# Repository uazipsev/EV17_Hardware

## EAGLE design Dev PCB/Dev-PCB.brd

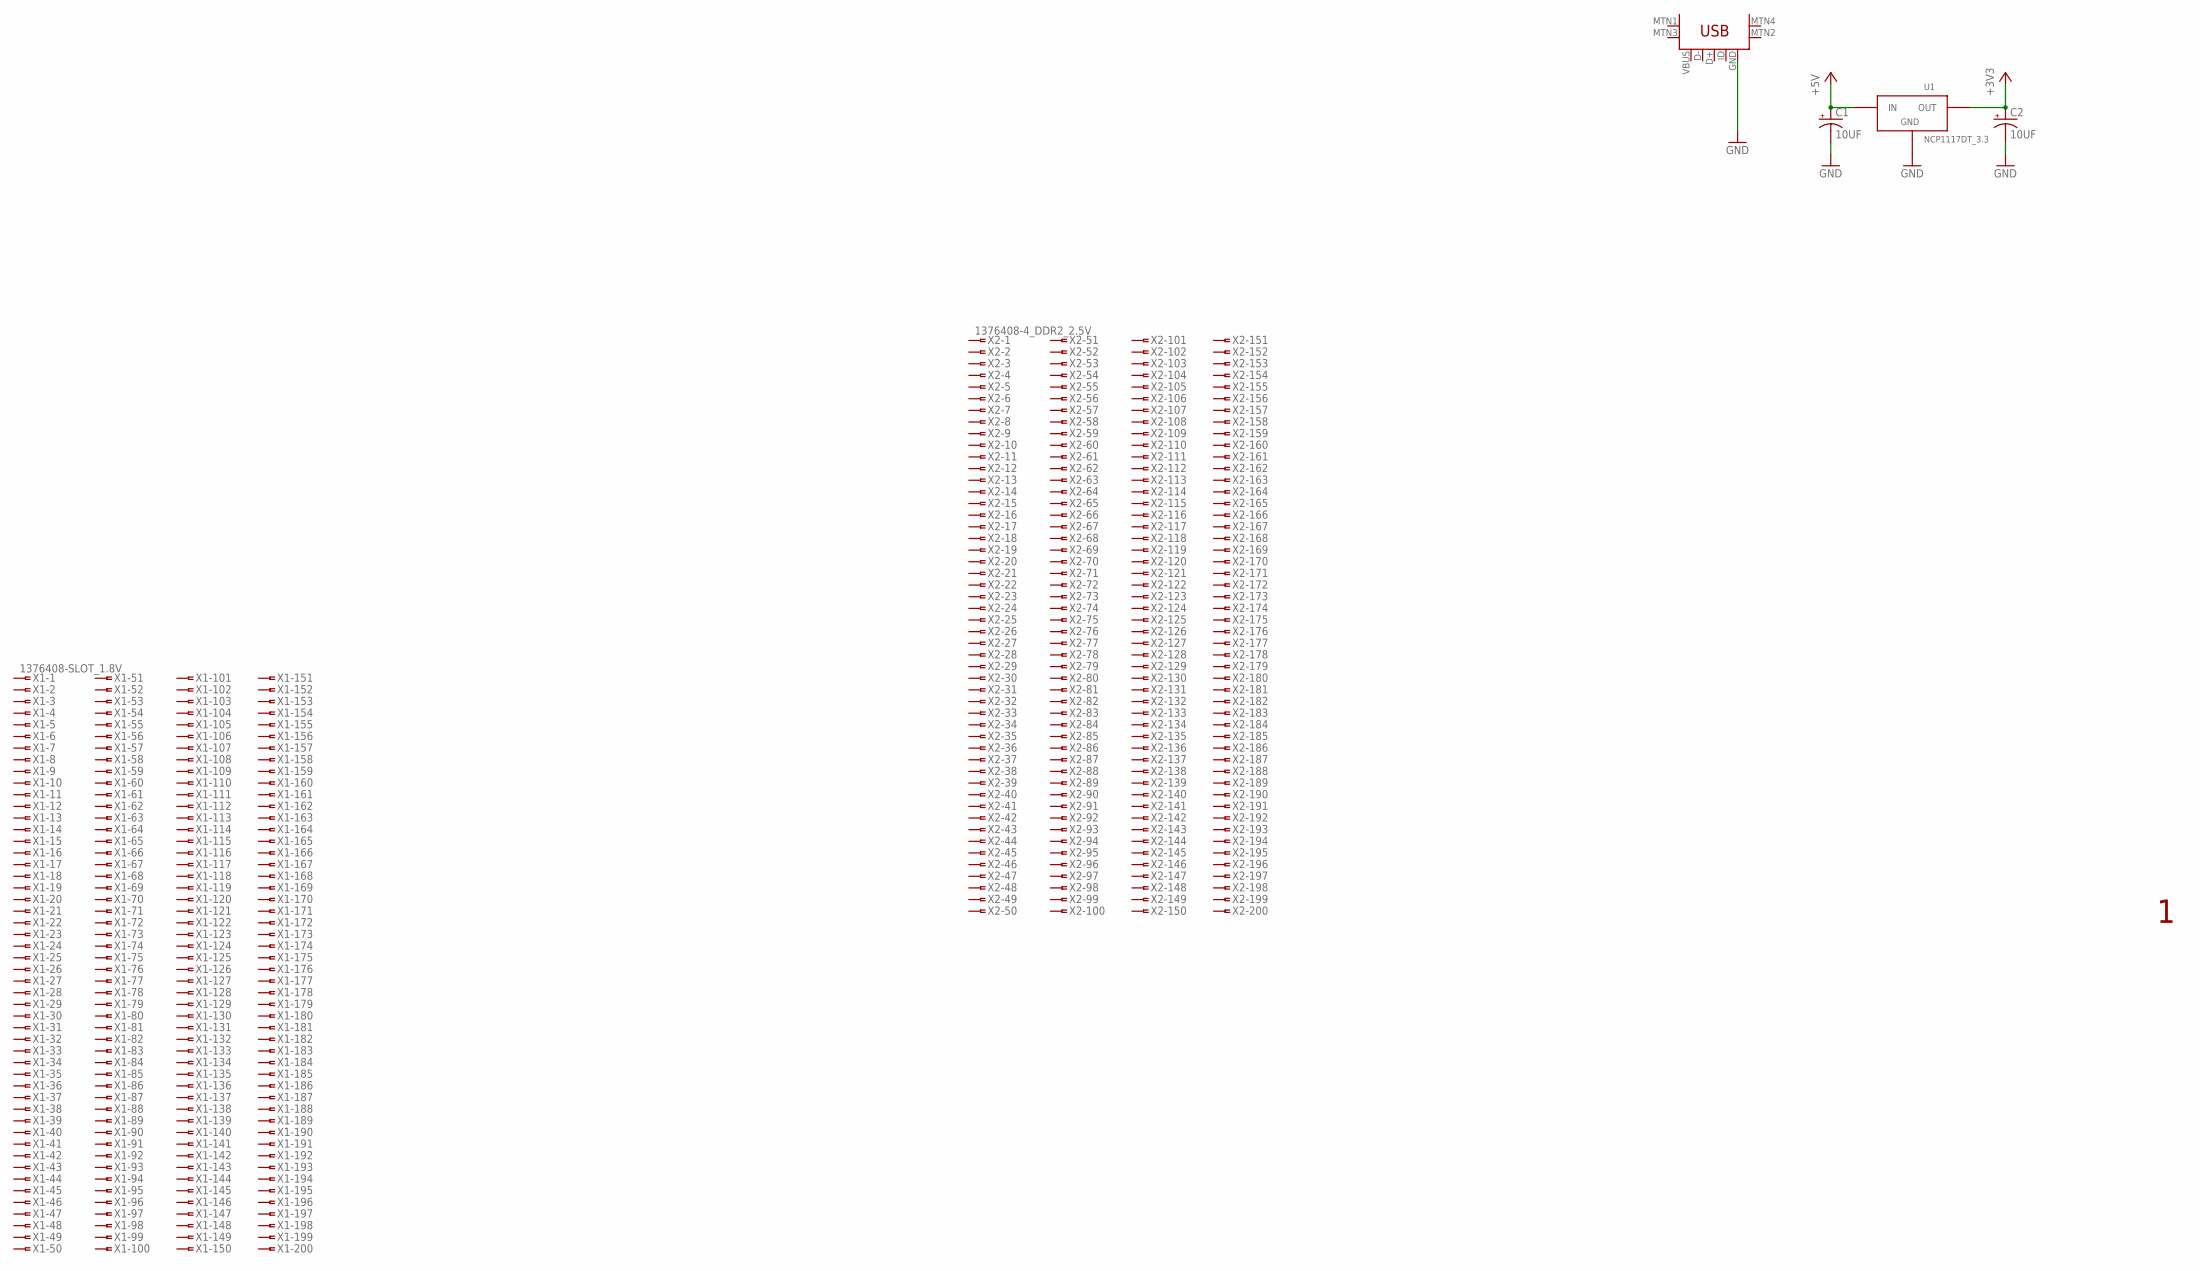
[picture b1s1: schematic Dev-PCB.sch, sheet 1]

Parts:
C1, C2: 10UF; EIA3216-16V
U1: NCP1117DT_3.3; DPAK
U$1: USB-MINIB-5PIN; USB-MINIB
X1: 1376408-SLOT_1.8V; SLOT-1376408-1_1.8V
X2: 1376408-4_DDR2_2.5V; 1-1376408-4

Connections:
+3V3: C2.A (+), U1.2 (OUT)
+5V: C1.A (+), U1.3 (IN)
GND: C1.C (+1), C2.C (+1), U1.1 (GND), U$1.GND

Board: 2 copper layers, 6 parts (0 on the bottom side), 3 nets, no tracks yet.

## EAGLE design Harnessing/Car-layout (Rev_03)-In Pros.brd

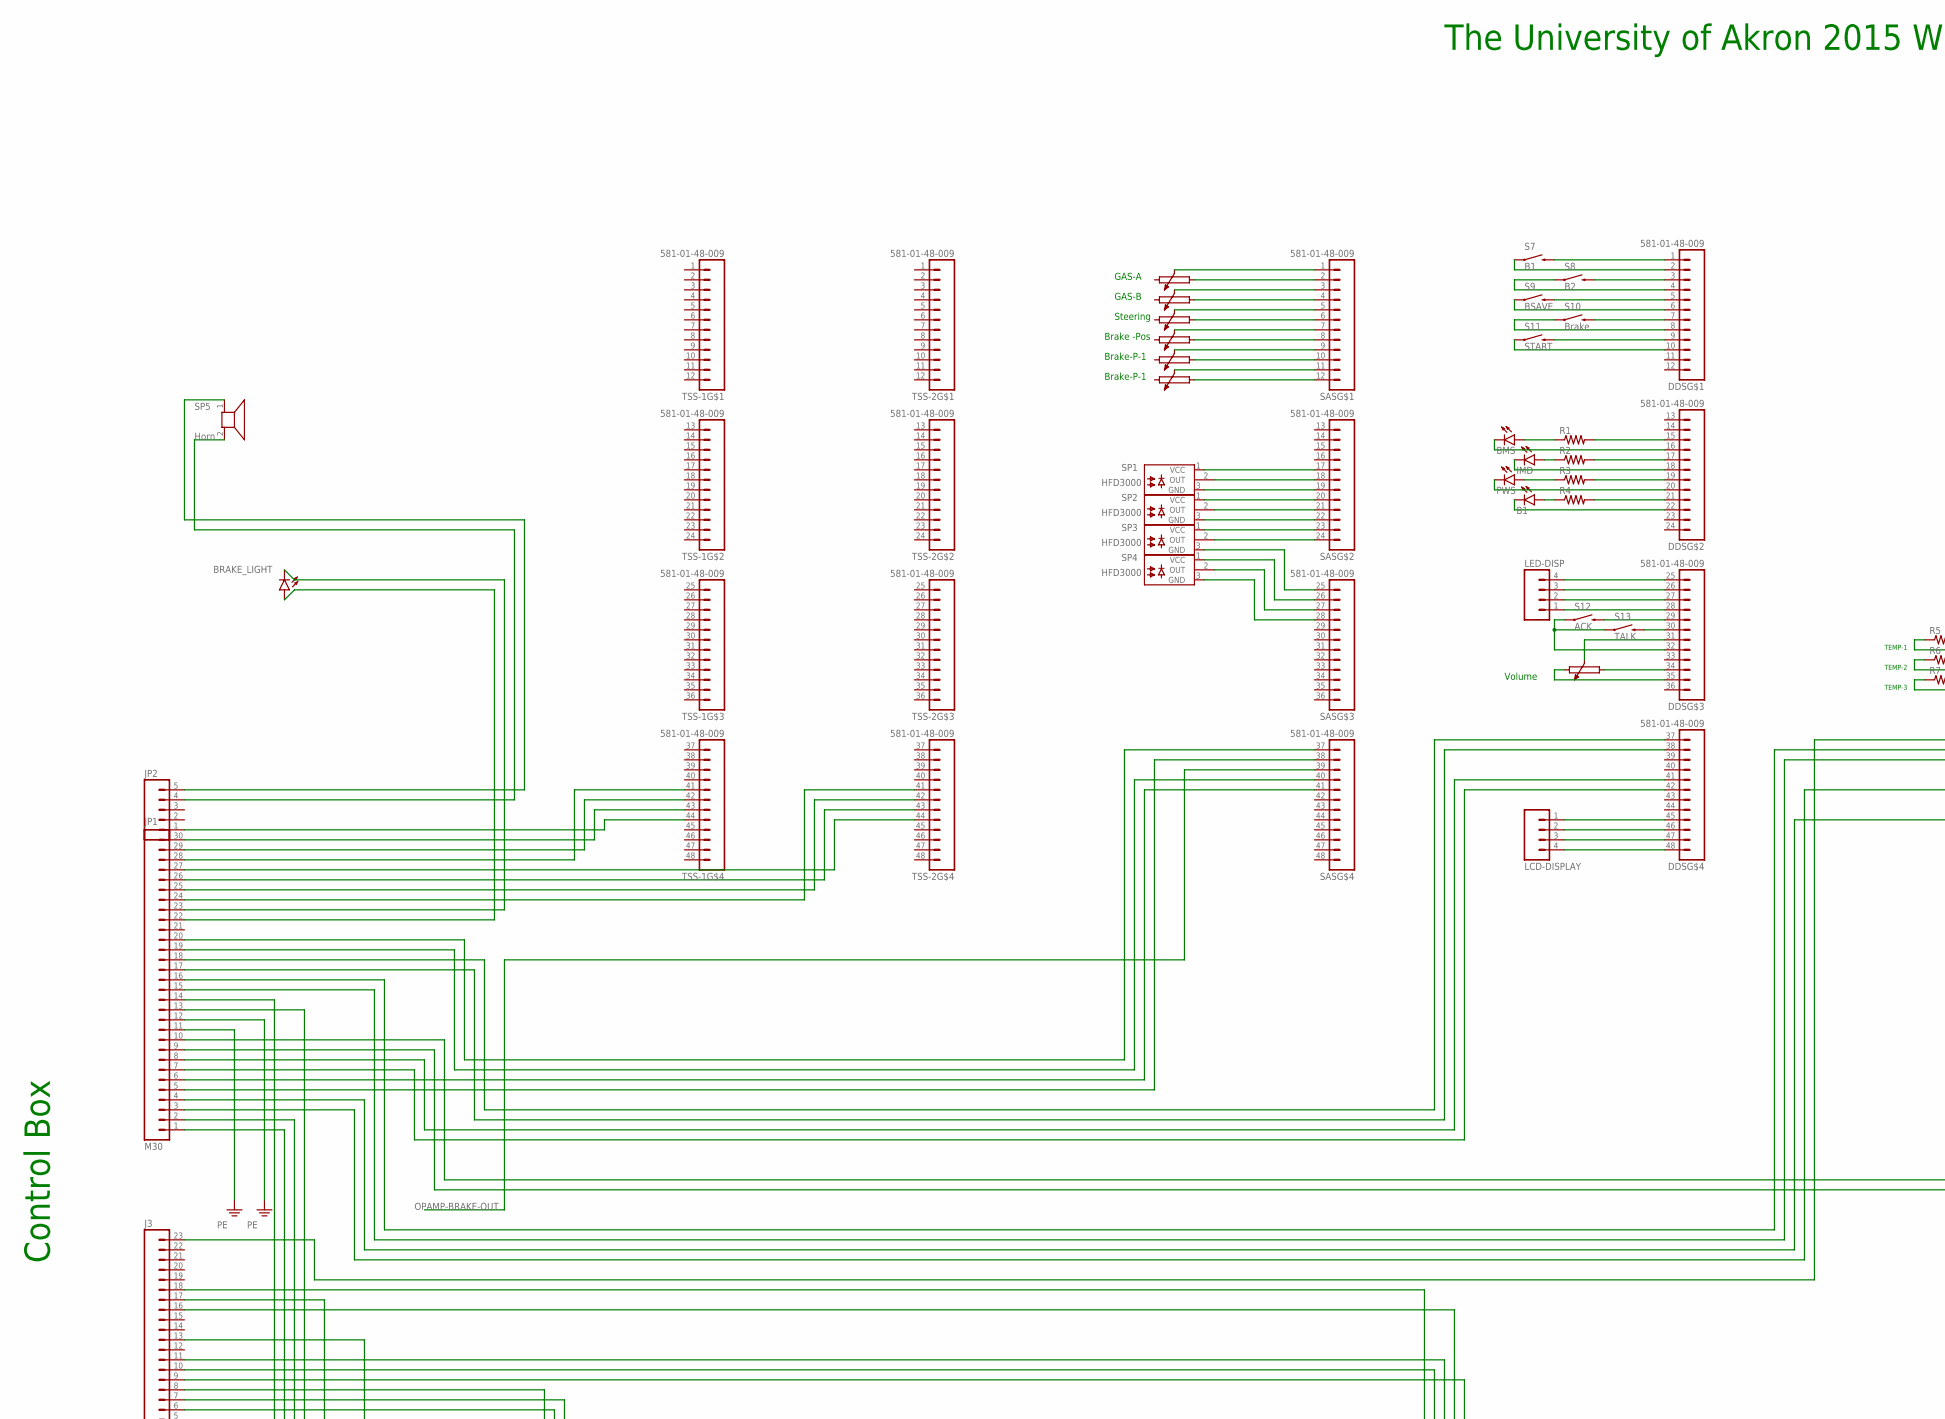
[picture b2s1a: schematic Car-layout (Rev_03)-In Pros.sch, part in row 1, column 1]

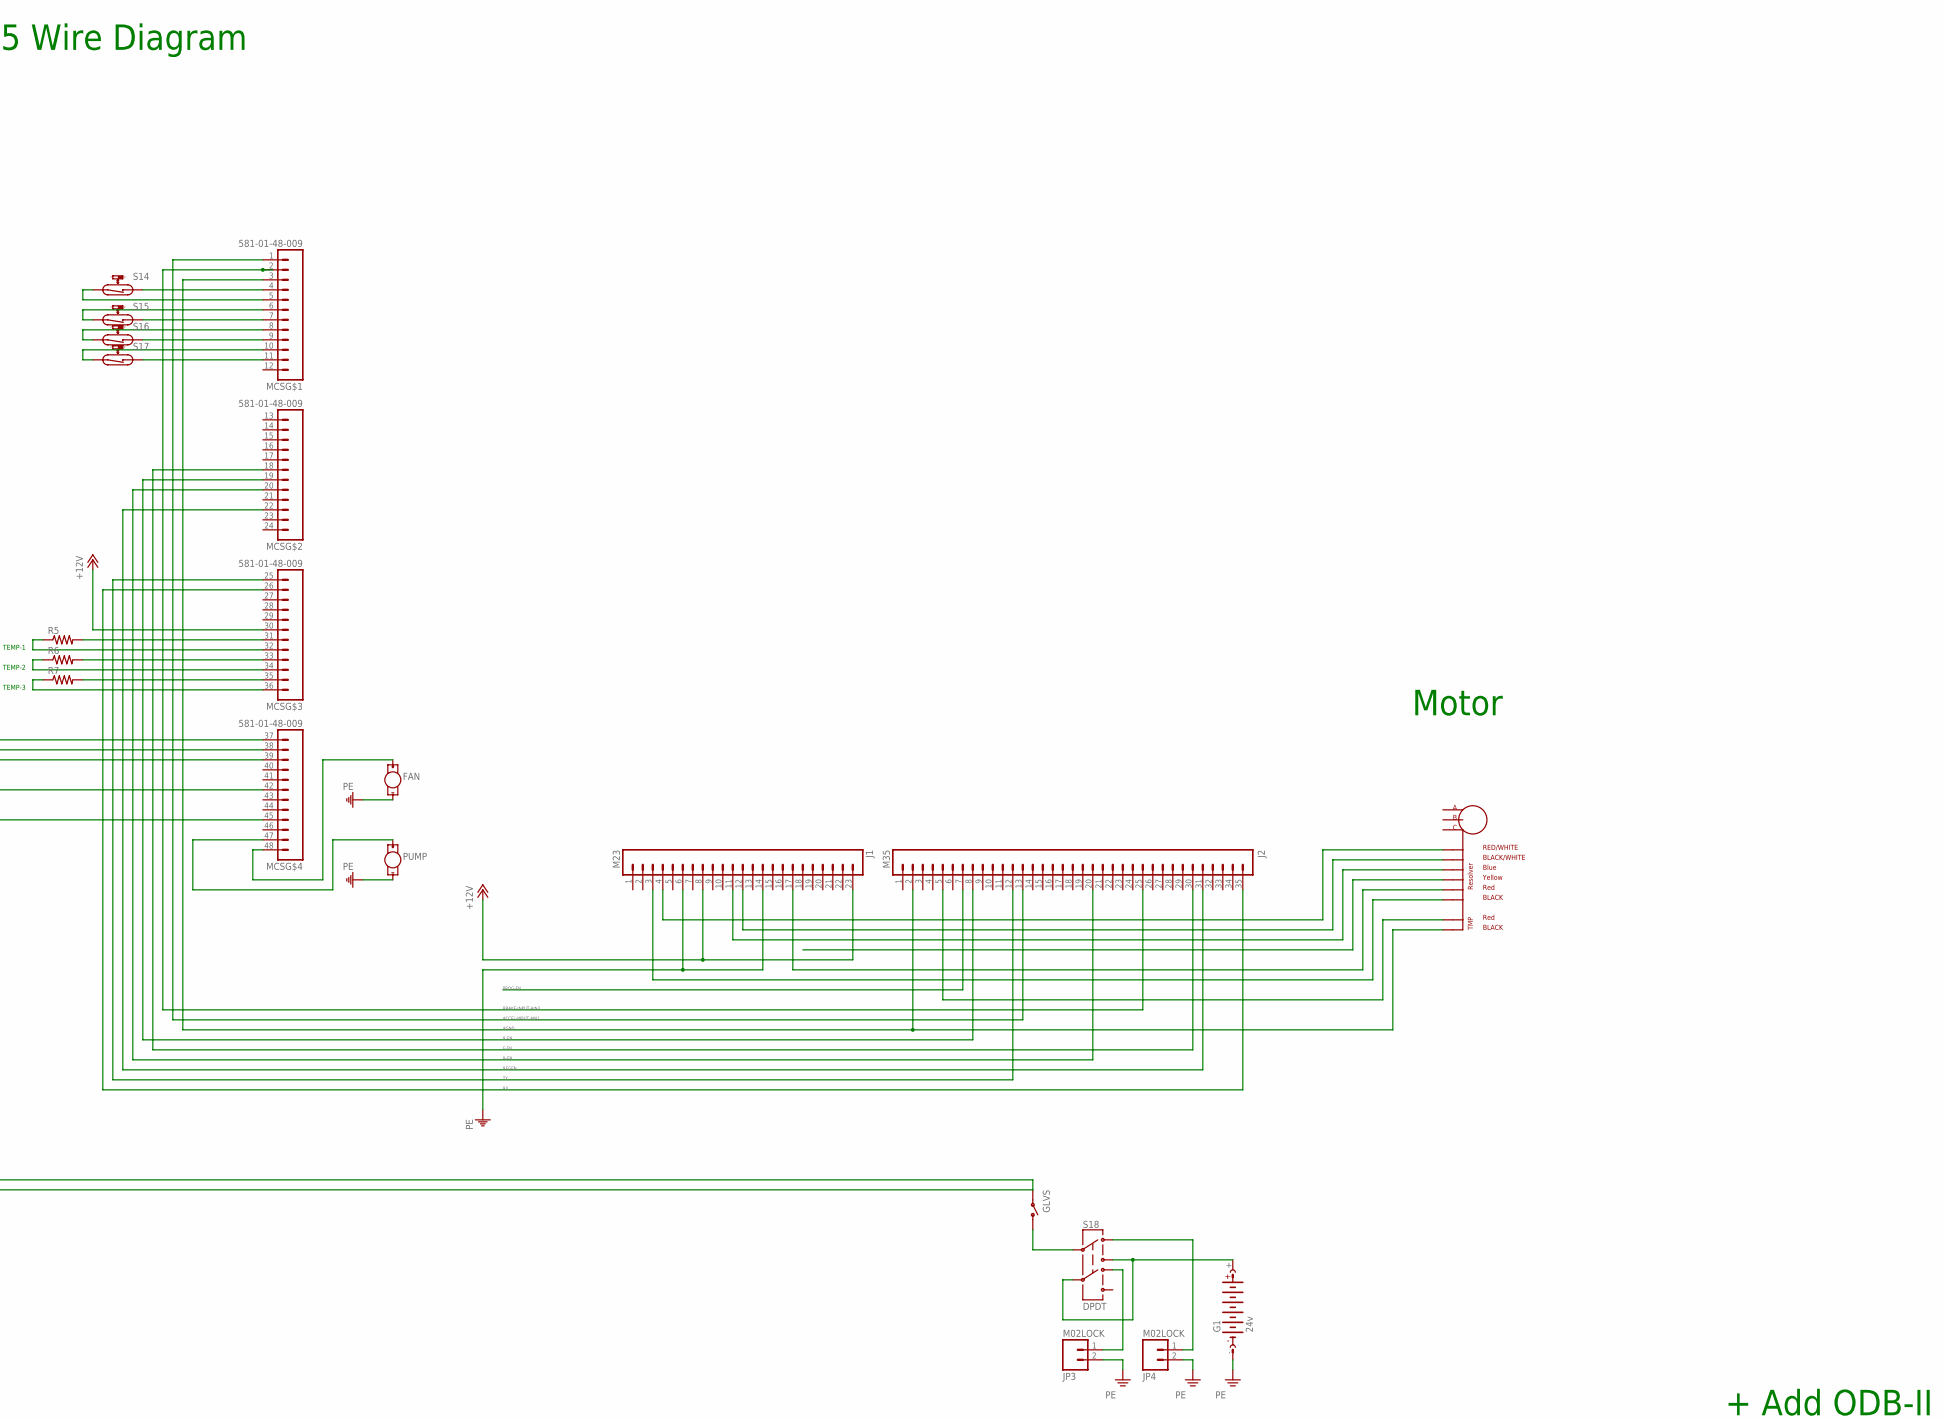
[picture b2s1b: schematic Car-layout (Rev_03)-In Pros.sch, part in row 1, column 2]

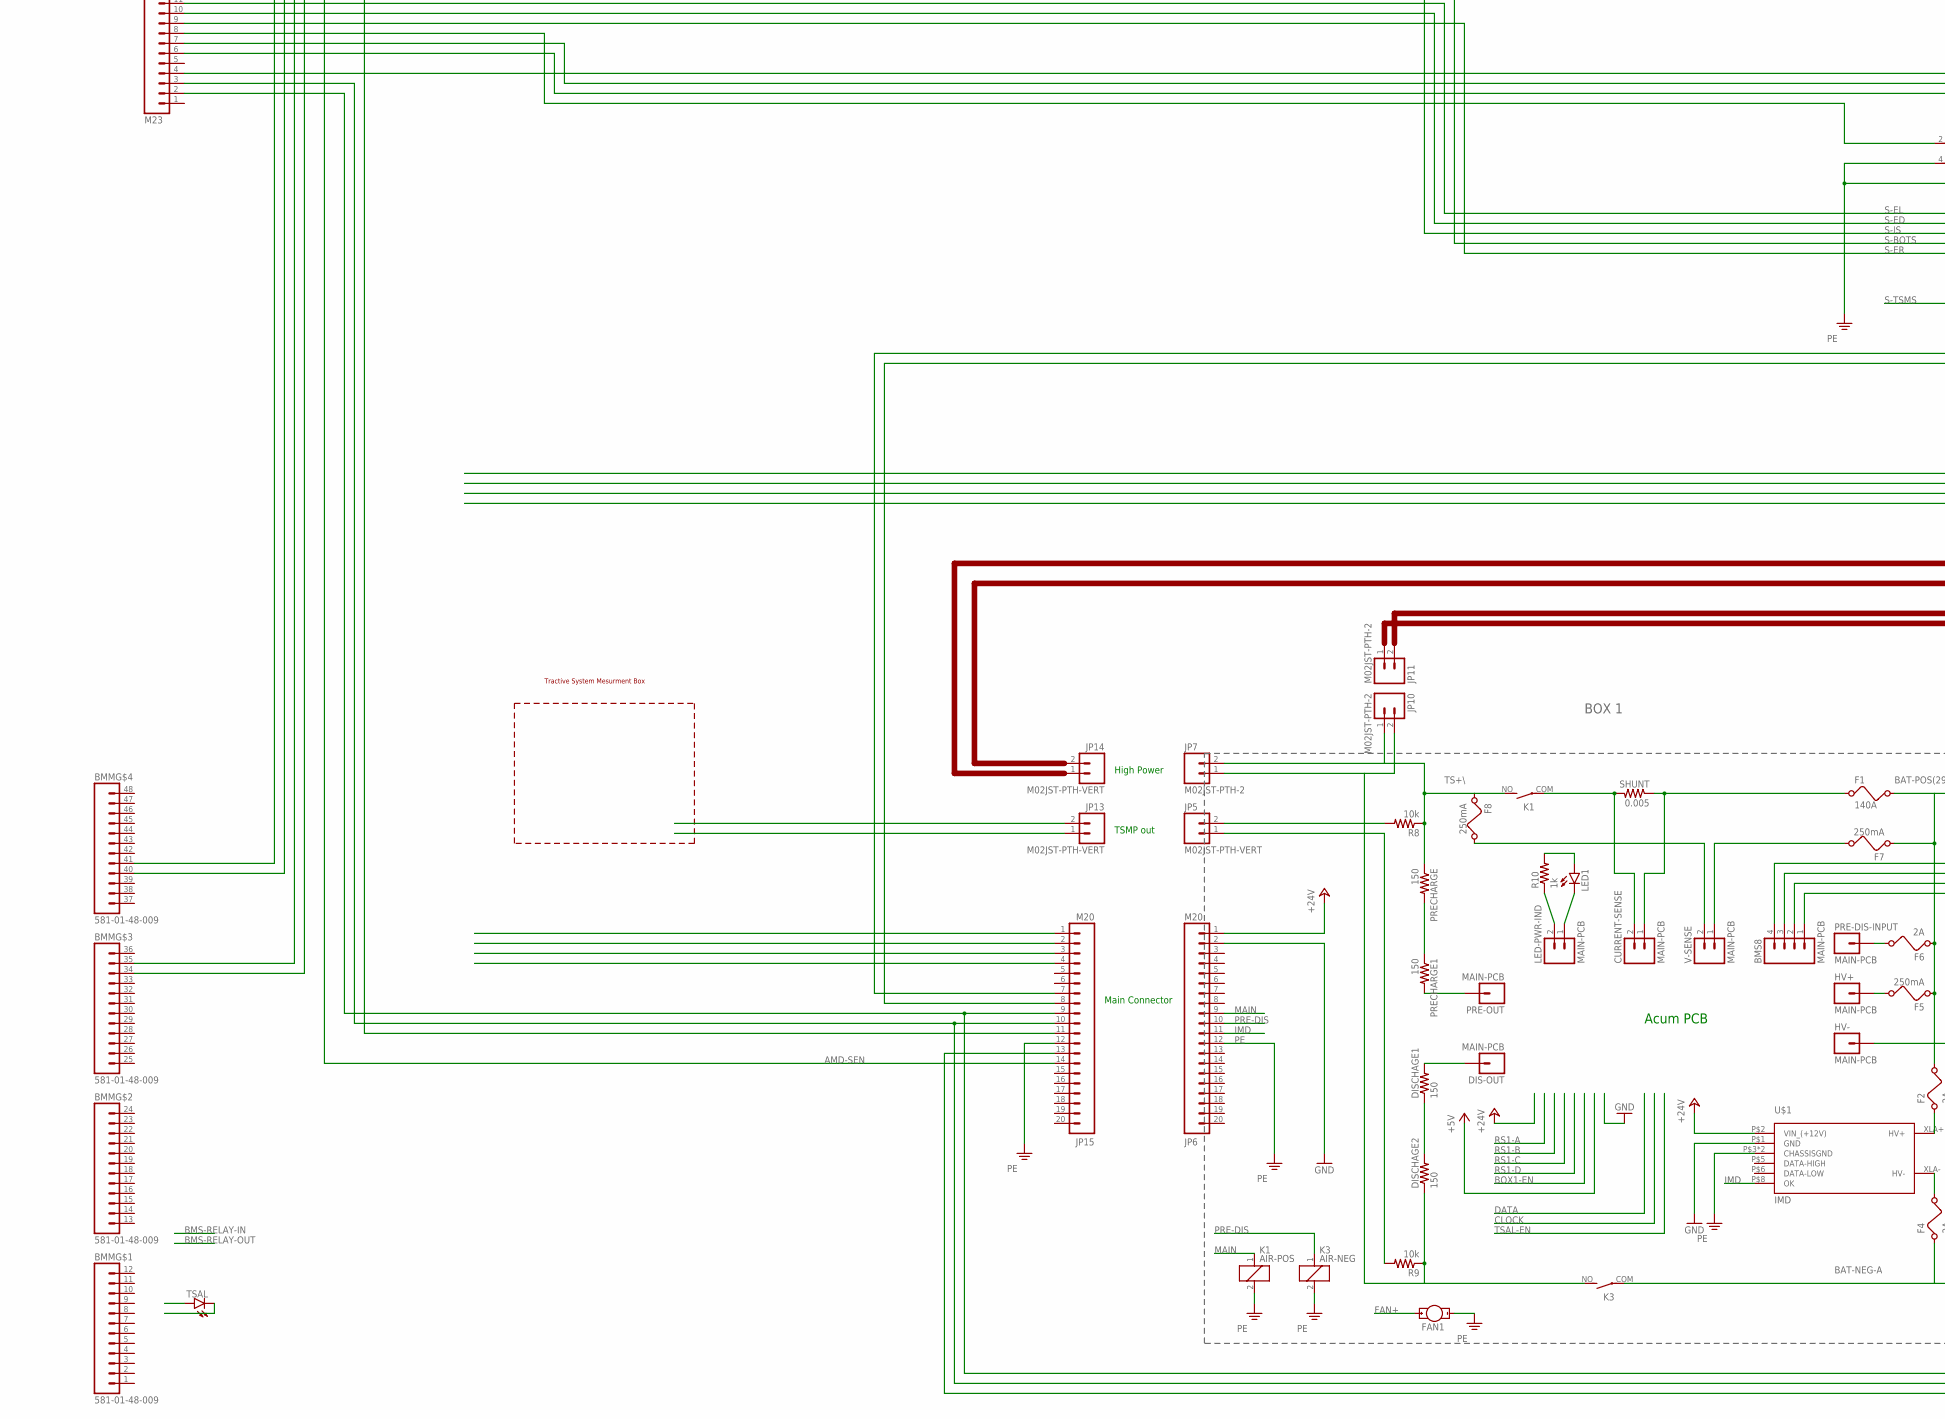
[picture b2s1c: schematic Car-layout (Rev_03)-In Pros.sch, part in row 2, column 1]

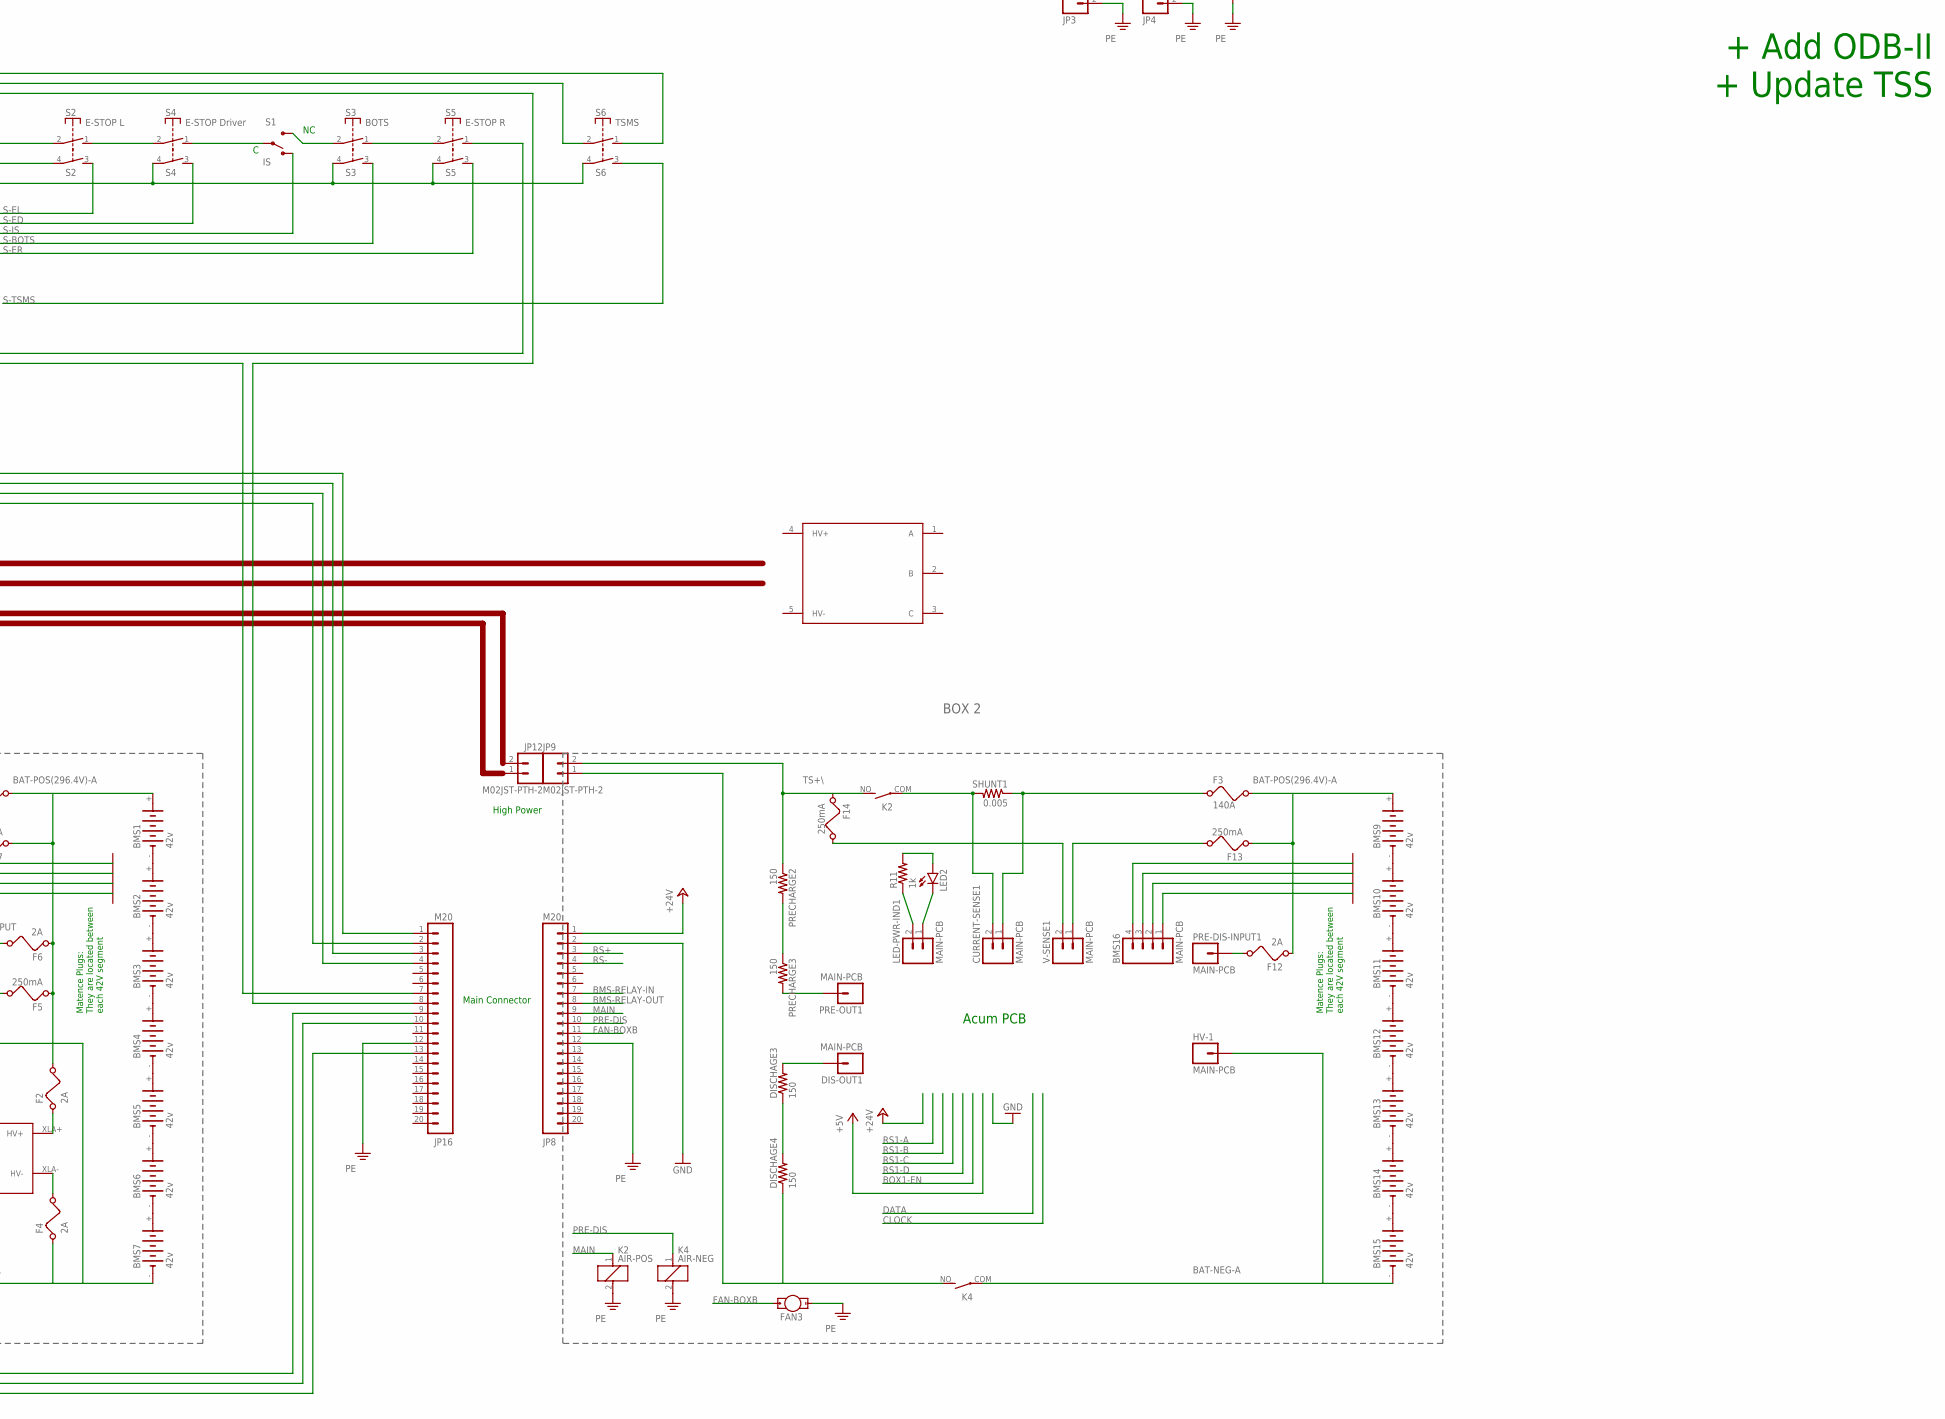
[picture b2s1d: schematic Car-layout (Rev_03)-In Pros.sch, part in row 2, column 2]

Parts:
B1: LED5MM
BMM: 581-01-48-009
BMS: LED5MM
BMS1, BMS2, BMS3, BMS4, BMS5, BMS6, BMS7, BMS9, BMS10, BMS11, BMS12, BMS13, BMS14, BMS15: 42v; VST4
BMS8, BMS16: MAIN-PCB; 1X04_LOCK_LONGPADS
BRAKE_LIGHT: LED5MM
CURRENT-SENSE, CURRENT-SENSE1: MAIN-PCB; JST-2-PTH-NS
DDS: 581-01-48-009
DIS-OUT, DIS-OUT1: MAIN-PCB; 1X01_OFFSET
DISCHAGE1, DISCHAGE2, DISCHAGE3, DISCHAGE4: 150; 0603-RES
F1, F3: 140A; FUSE
F2, F4, F6, F12: 2A; FUSE
F5, F7, F8, F13, F14: 250mA; FUSE
FAN, FAN1, FAN3: MOTOR10MM; VIBE-MOTOR-10MM
G1: 24v; AB9V
GLVS: SWITCH-SPST-2TV; SWITCH-SPST-VERTICAL
HV+: MAIN-PCB; 1X01_OFFSET
HV-, HV-1: MAIN-PCB; 1X01_OFFSET
IMD: LED5MM
J1, J3: M23; 1-770669-1
J2: M35; 1-776163-2
JP1: M30; 1X30
JP2: M05LOCK; 1X05_LOCK
JP3, JP4: M02LOCK; 1X02_LOCK
JP5, JP13, JP14: M02JST-PTH-VERT; JST-2-PTH-VERT
JP6, JP8, JP15, JP16: M20; 1X20
JP7, JP9, JP10, JP11, JP12: M02JST-PTH-2; JST-2-PTH
K1, K2: AIR-POS; APF30212A
K3, K4: AIR-NEG; APF30212A
LCD-DISPLAY: M04LONGPADS; 1X04_LONGPADS
LED1, LED2: LED5MM
LED-DISP: M04LONGPADS; 1X04_LONGPADS
LED-PWR-IND, LED-PWR-IND1: MAIN-PCB; JST-2-PTH-NS
M1: MOTOR-3PHASE; MC3PHASE
MC-1: PM100DX; MC-5
MCS: 581-01-48-009
PRE-DIS-INPUT, PRE-DIS-INPUT1: MAIN-PCB; 1X01_OFFSET
PRE-OUT, PRE-OUT1: MAIN-PCB; 1X01_OFFSET
PRECHARGE, PRECHARGE1, PRECHARGE2, PRECHARGE3: 150; 0603-RES
PUMP: MOTOR10MM; VIBE-MOTOR-10MM
PWS: LED5MM
R1, R2, R3, R4, R5, R6, R7: RESISTOR0805-RES; 0805
R8, R9: 10k; 0805
R10, R11: 1k; 0603-RES
S1: IS; SWITCHE-DPDT
S2: E-STOP L; PVA1F
S3: BOTS; PVA1F
S4: E-STOP Driver; PVA1F
S5: E-STOP R; PVA1F
S6: TSMS; PVA1F
S7: B1; TACTILE-PTH
S8: B2; TACTILE-PTH
S9: BSAVE; TACTILE-PTH
S10: Brake; TACTILE-PTH
S11: START; TACTILE-PTH
S12: ACK; TACTILE-PTH
S13: TALK; TACTILE-PTH
S14, S15, S16, S17: REED-SWITCH-CT10-1530-G1; CT10-G1
S18: DPDT; AYZ0202
SAS: 581-01-48-009
SHUNT, SHUNT1: 0.005; 0603-RES
SP1, SP2, SP3, SP4: HFD3000; TO46-FW3
SP5: Horn; AL23P
TSAL: LED5MM
TSS-1, TSS-2: 581-01-48-009
U$1: IMD
V-SENSE, V-SENSE1: MAIN-PCB; JST-2-PTH-NS

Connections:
+12V: J1.8, J1.23, MCS.30 (6)
+24V: JP6.1, JP8.1, U$1.P$2 (VIN_(+12V))
ACCEL-INPUT-AIN1: J2.13, MCS.1
AGND: J2.2, M1.9, MCS.3
AMD-SEN: J3.17, JP15.14
B-EN: J2.20, MCS.20 (8)
BAT-NEG-A: BMS7.-, BMS15.-, F4.1, HV-.1, HV-1.1, K3.COM, K4.COM
BAT-POS(296.4V)-A: BMS1.+, BMS9.+, F1.2, F2.2, F3.2, F5.1, F6.1, F7.1, F12.1, F13.1
BMS-RELAY-IN: JP8.7
BMS-RELAY-OUT: JP8.8
BRAKE-INPUT-AIN3: J2.25, MCS.2
F-EN: J2.30, MCS.18 (6)
FAN+: FAN1.+
FAN-BOXB: FAN3.+, JP8.11
GND: JP6.2, JP8.2, U$1.P$1 (GND)
IMD: JP6.11, U$1.P$8 (OK)
MAIN: JP6.9, JP8.9, K1.1, K2.1
MP1: BMS1.-, BMS2.+
MP2: BMS9.-, BMS10.+
unnamed: J3.8, S2.2
unnamed: S2.1 (S), S4.2
unnamed: S1.2, S4.1 (S)
unnamed: S1.3 (S), S3.2
unnamed: S3.1 (S), S5.2
unnamed: J3.6, JP16.8
unnamed: J3.7, S6.2
unnamed: J3.4, S6.1 (S)
unnamed: J3.13, JP15.11
unnamed: SAS.23 (11), SP3.1 (VCC)
unnamed: SAS.24 (12), SP3.2 (OUT)
unnamed: SAS.25 (1), SP3.3 (GND)
unnamed: SAS.17 (5), SP1.1 (VCC)
unnamed: SAS.19 (7), SP1.3 (GND)
unnamed: SAS.18 (6), SP1.2 (OUT)
unnamed: SAS.20 (8), SP2.1 (VCC)
unnamed: SAS.22 (10), SP2.3 (GND)
unnamed: SAS.21 (9), SP2.2 (OUT)
unnamed: SAS.26 (2), SP4.1 (VCC)
unnamed: SAS.27 (3), SP4.2 (OUT)
unnamed: SAS.28 (4), SP4.3 (GND)
unnamed: JP1.20, SAS.37 (1)
unnamed: JP1.5, SAS.38 (2)
unnamed: JP1.19, SAS.40 (4)
unnamed: JP1.6, SAS.41 (5)
unnamed: DDS.1, S7.3 (2)
unnamed: DDS.2, S7.1
unnamed: DDS.3, S8.3 (2)
unnamed: DDS.4, S8.1
unnamed: DDS.5, S9.3 (2)
unnamed: DDS.6, S9.1
unnamed: DDS.7, S10.3 (2)
unnamed: DDS.8, S10.1
unnamed: DDS.9, S11.3 (2)
unnamed: DDS.10, S11.1
unnamed: IMD.A, R2.1
unnamed: DDS.17 (5), R2.2
unnamed: DDS.18 (6), IMD.K (C)
unnamed: BMS.A, R1.1
unnamed: DDS.15 (3), R1.2
unnamed: BMS.K (C), DDS.16 (4)
unnamed: PWS.A, R3.1
unnamed: DDS.19 (7), R3.2
unnamed: DDS.20 (8), PWS.K (C)
unnamed: B1.A, R4.1
unnamed: DDS.21 (9), R4.2
unnamed: B1.K (C), DDS.22 (10)
unnamed: DDS.28 (4), LED-DISP.1
unnamed: DDS.27 (3), LED-DISP.2
unnamed: DDS.26 (2), LED-DISP.3
unnamed: DDS.25 (1), LED-DISP.4
unnamed: DDS.32 (8), S12.1, S13.1
unnamed: DDS.29 (5), S12.3 (2)
unnamed: DDS.30 (6), S13.3 (2)
unnamed: DDS.41 (5), JP1.8
unnamed: DDS.42 (6), JP1.7
unnamed: DDS.37 (1), JP1.18
unnamed: DDS.38 (2), JP1.17
unnamed: DDS.48 (12), LCD-DISPLAY.4
unnamed: DDS.47 (11), LCD-DISPLAY.3
unnamed: DDS.46 (10), LCD-DISPLAY.2
unnamed: DDS.45 (9), LCD-DISPLAY.1
unnamed: GLVS.2, JP1.9, JP1.10
unnamed: GLVS.1 (O), S18.2
unnamed: BMM.41 (5), JP1.14
unnamed: BMM.40 (4), JP1.1
unnamed: BMM.34 (10), JP1.13
unnamed: J2.5, M1.8
unnamed: J3.23, MCS.37 (1)
unnamed: J1.17, M1.10
unnamed: J1.3, M1.11
unnamed: J1.11, M1.6
unnamed: J1.12, M1.5
unnamed: J1.4, M1.4
unnamed: FAN.+, MCS.48 (12)
unnamed: MCS.47 (11), PUMP.+
unnamed: MCS.31 (7), R5.2
unnamed: MCS.32 (8), R5.1
unnamed: MCS.34 (10), R6.1
unnamed: MCS.33 (9), R6.2
unnamed: MCS.36 (12), R7.1
unnamed: MCS.35 (11), R7.2
unnamed: MCS.4, S14.1
unnamed: MCS.5, S14.2
unnamed: MCS.7, S15.1
unnamed: MCS.6, S15.2
unnamed: MCS.9, S16.1
unnamed: MCS.8, S16.2
unnamed: MCS.11, S17.1
unnamed: MCS.10, S17.2
unnamed: JP4.1, S18.1
unnamed: G1.+, S18.3, S18.5
unnamed: JP3.1, S18.4
unnamed: JP2.5, SP5.1
unnamed: JP2.4, SP5.2
unnamed: JP1.28, TSS-1.41 (5)
unnamed: JP2.1, TSS-1.44 (8)
unnamed: JP1.29, TSS-1.42 (6)
unnamed: JP1.30, TSS-1.43 (7)
unnamed: JP1.27, TSS-2.44 (8)
unnamed: JP1.26, TSS-2.43 (7)
unnamed: JP1.25, TSS-2.42 (6)
unnamed: JP1.24, TSS-2.41 (5)
unnamed: BMS2.-, BMS3.+
unnamed: BMS3.-, BMS4.+
unnamed: BMS4.-, BMS5.+
unnamed: BMS5.-, BMS6.+
unnamed: BMS6.-, BMS7.+
unnamed: JP5.2, R8.2
unnamed: JP5.1, R9.2
unnamed: F4.2, U$1.XLA- (HV-)
unnamed: F2.1, U$1.XLA+ (HV+)
unnamed: CURRENT-SENSE.2, K1.COM, SHUNT.2
unnamed: CURRENT-SENSE.1, F1.1, SHUNT.1
unnamed: F5.2, HV+.1
unnamed: LED-PWR-IND.2, R10.1
unnamed: LED1.A, R10.2
unnamed: LED1.K (C), LED-PWR-IND.1
unnamed: F6.2, PRE-DIS-INPUT.1
unnamed: F7.2, V-SENSE.1
unnamed: F8.2, V-SENSE.2
unnamed: DISCHAGE2.1, JP7.1, JP10.2, K3.NO (S), R9.1
unnamed: PRECHARGE.2, PRECHARGE1.1
unnamed: PRE-OUT.1, PRECHARGE1.2
unnamed: DIS-OUT.1, DISCHAGE1.2
unnamed: DISCHAGE1.1, DISCHAGE2.2
unnamed: BMS10.-, BMS11.+
unnamed: BMS11.-, BMS12.+
unnamed: BMS12.-, BMS13.+
unnamed: BMS13.-, BMS14.+
unnamed: BMS14.-, BMS15.+
unnamed: CURRENT-SENSE1.2, K2.COM, SHUNT1.2
unnamed: CURRENT-SENSE1.1, F3.1, SHUNT1.1
unnamed: LED-PWR-IND1.2, R11.1
unnamed: LED2.A, R11.2
unnamed: LED2.K (C), LED-PWR-IND1.1
unnamed: F12.2, PRE-DIS-INPUT1.1
unnamed: F13.2, V-SENSE1.1
unnamed: F14.2, V-SENSE1.2
unnamed: DISCHAGE4.1, JP9.1, K4.NO (S)
unnamed: PRECHARGE2.2, PRECHARGE3.1
unnamed: PRE-OUT1.1, PRECHARGE3.2
unnamed: DIS-OUT1.1, DISCHAGE3.2
unnamed: DISCHAGE3.1, DISCHAGE4.2
unnamed: BMM.35 (11), JP1.2
unnamed: BRAKE_LIGHT.K (C), JP1.23
unnamed: JP15.7, S5.1 (S)
unnamed: JP15.8, JP16.7
unnamed: BRAKE_LIGHT.A, JP1.22
unnamed: J3.3, JP15.10, JP16.10
unnamed: JP15.13, JP16.13
unnamed: J3.2, JP15.9, JP16.9
unnamed: JP1.3, MCS.42 (6)
unnamed: JP1.4, MCS.45 (9)
unnamed: JP1.15, MCS.39 (3)
unnamed: JP1.16, MCS.38 (2)
OPAMP-BRAKE-OUT: SAS.39 (3)
PE: FAN.-, FAN1.-, FAN3.-, G1.-, J1.6, J1.14, JP1.11, JP1.12, JP3.2, JP4.2, JP6.12, JP8.12, JP15.12, JP16.12, K1.2, K2.2, K3.2, K4.2, PUMP.-, S2.4, S3.4, S4.4, S5.4, S6.4, U$1.P$3 (CHASSISGND), U$1.P$4 (CHASSISGND)
PRE-DIS: JP6.10, JP8.10, K3.1, K4.1
PROG-EN: J2.7
R-EN: J2.8, MCS.19 (7)
REGEN: J2.31, MCS.22 (10)
RS+: JP8.3
RS-: JP8.4
RX: J2.35, MCS.26 (2)
S-BOTS: J3.16, S3.3 (S)
S-ED: J3.10, S4.3 (S)
S-EL: J3.11, S2.3 (S)
S-ER: J3.9, S5.3 (S)
S-IS: J3.18, S1.1 (O)
S-TSMS: S6.3 (S)
TS+\: F8.1, F14.1, JP7.2, JP9.2, JP10.1, K1.NO (S), K2.NO (S), PRECHARGE.1, PRECHARGE2.1, R8.1
TX: J2.12, MCS.25 (1)

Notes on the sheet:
GAS-A
GAS-B
Steering
Brake -Pos
Brake-P-1
Control Box
Volume
TEMP-1
TEMP-2
TEMP-3
BOX 1
Matence Plugs: They are located between each 42V segment
High Power
TSMP out
Main Connector
Acum PCB
BOX 2
Tractive System Mesurment Box
Motor
The University of Akron 2015 Wire Diagram
+ Add ODB-II + Update TSS

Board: 2 copper layers, 134 parts (0 on the bottom side), 184 nets, no tracks yet.

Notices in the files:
parts and their libraries:
SparkFun-Connectors: Licensing: CC v3.0 Share-Alike You are welcome to use this library for commercial purposes.
SparkFun-Connectors: Licensing: Creative Commons ShareAlike 4.0 International - https://creativecommons.org/licenses/by-sa/4.0
